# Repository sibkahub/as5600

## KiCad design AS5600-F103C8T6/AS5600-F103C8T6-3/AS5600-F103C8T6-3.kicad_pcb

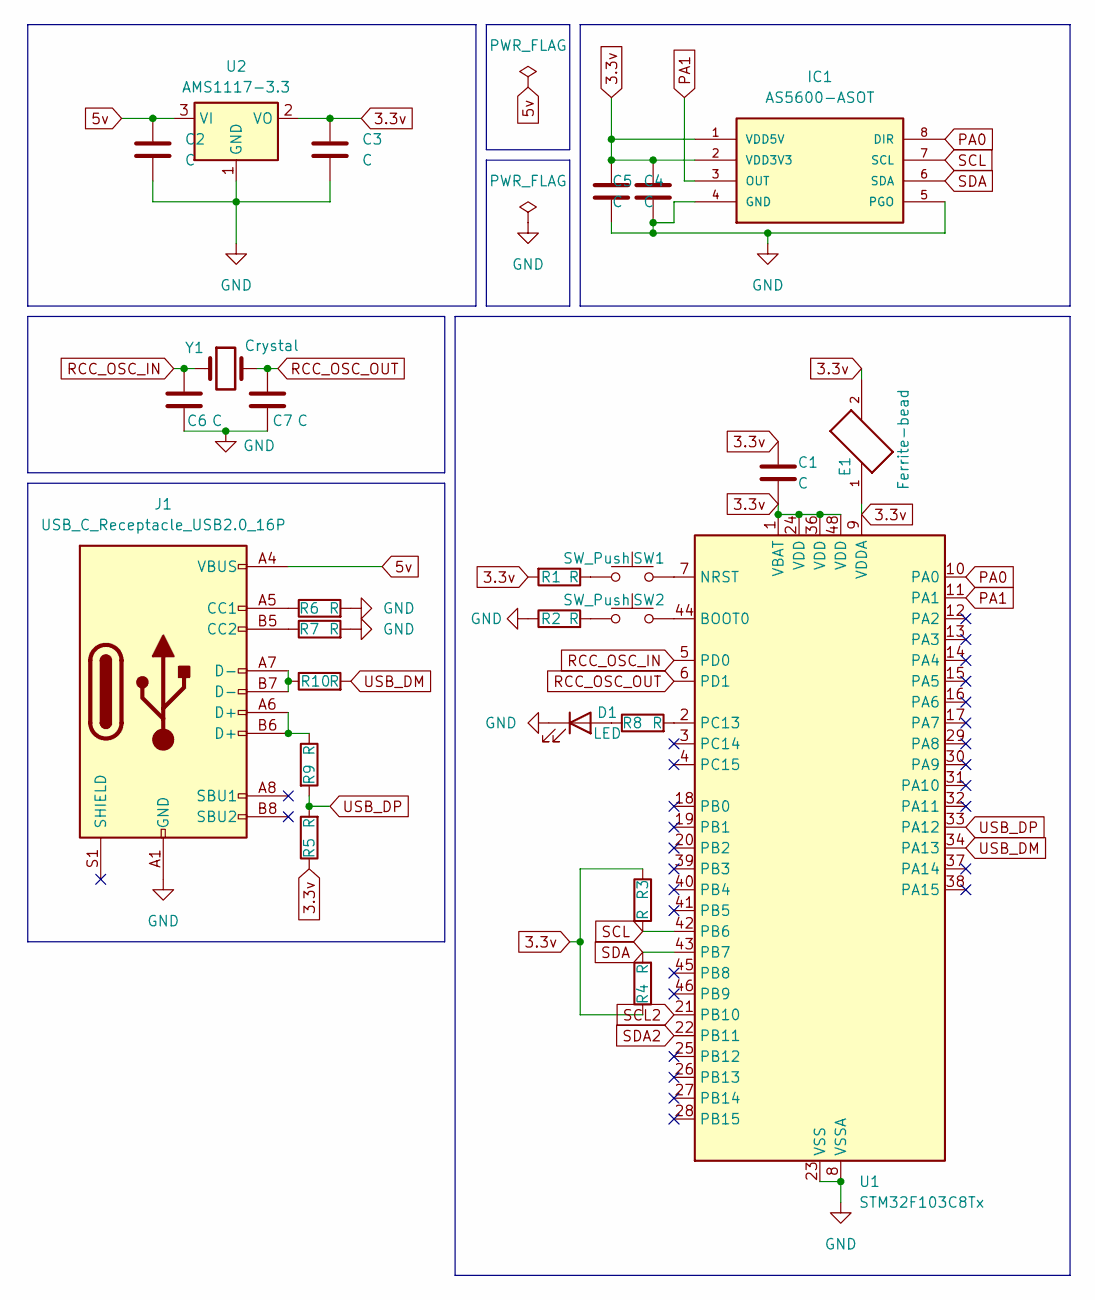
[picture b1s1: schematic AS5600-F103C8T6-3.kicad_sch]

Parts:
C1, C2, C3, C4, C5, C6, C7: C; C_0603_1608Metric
D1: LED; LED_0603_1608Metric
E1: Ferrite-bead; 0603_ferrite_chip; PARTREV C
IC1: AS5600-ASOT; SOIC127P600X175-8N; MOUSER_PART_NUMBER 985-AS5600-ASOT
J1: USB_C_Receptacle_USB2.0_16P; USB_C_Receptacle_GCT_USB4105-xx-A_16P_TopMnt_Horizontal
R1, R2, R3, R4, R5, R6, R7, R8, R9, R10: R; R_0603_1608Metric
SW1, SW2: SW_Push; SW_Push_SPST_NO_Alps_SKRK
U1: STM32F103C8Tx; LQFP-48_7x7mm_P0.5mm
U2: AMS1117-3.3; SOT-223-3_TabPin2
Y1: Crystal; Crystal_SMD_Abracon_ABM7-2Pin_6.0x3.5mm

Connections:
3.3v: C1.1, C1.2, C3.2, C4.1, C5.1, E1.1, E1.2, IC1.1 (VDD5V), IC1.2 (VDD3V3), R1.2, R3.1, R4.1, R5.1, U1.1 (VBAT), U1.9 (VDDA), U1.24 (VDD), U1.36 (VDD), U1.48 (VDD), U2.2 (VO)
5v: C2.1, J1.A4 (VBUS), J1.A9 (VBUS), J1.B4 (VBUS), J1.B9 (VBUS), U2.3 (VI)
GND: C2.2, C3.1, C4.2, C5.2, C6.2, C7.2, D1.1 (K), IC1.4 (GND), IC1.5 (PGO), J1.A1 (GND), J1.A12 (GND), J1.B1 (GND), J1.B12 (GND), R2.1, R6.2, R7.2, U1.8 (VSSA), U1.23 (VSS), U1.35 (VSS), U1.47 (VSS), U2.1 (GND)
unnamed: D1.2 (A), R8.1
unnamed: J1.A5 (CC1), R6.1
unnamed: J1.B5 (CC2), R7.1
unnamed: J1.A6 (D+), J1.B6 (D+), R9.1
unnamed: J1.A7 (D-), J1.B7 (D-), R10.1
unnamed: R1.1, SW1.1
unnamed: R2.2, SW2.1
unnamed: SW2.2, U1.44 (BOOT0)
unnamed: SW1.2, U1.7 (NRST)
unnamed: R8.2, U1.2 (PC13)
PA0: IC1.8 (DIR), U1.10 (PA0)
PA1: IC1.3 (OUT), U1.11 (PA1)
RCC_OSC_IN: C6.1, U1.5 (PD0), Y1.1
RCC_OSC_OUT: C7.1, U1.6 (PD1), Y1.2
SCL: IC1.7 (SCL), R3.2, U1.42 (PB6)
SCL2: U1.21 (PB10)
SDA: IC1.6 (SDA), R4.2, U1.43 (PB7)
SDA2: U1.22 (PB11)
USB_DM: R10.2, U1.34 (PA13)
USB_DP: R5.2, R9.2, U1.33 (PA12)

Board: 2 copper layers, 26 parts (17 on the bottom side), 21 nets, no tracks yet.
